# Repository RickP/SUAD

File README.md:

# Shut up and die!

A hardware version of a bomb defusing game.

Made with a custom board and a Raspberry Pi Pico.
The firmware supplies the manual over a USB mass storage medium.

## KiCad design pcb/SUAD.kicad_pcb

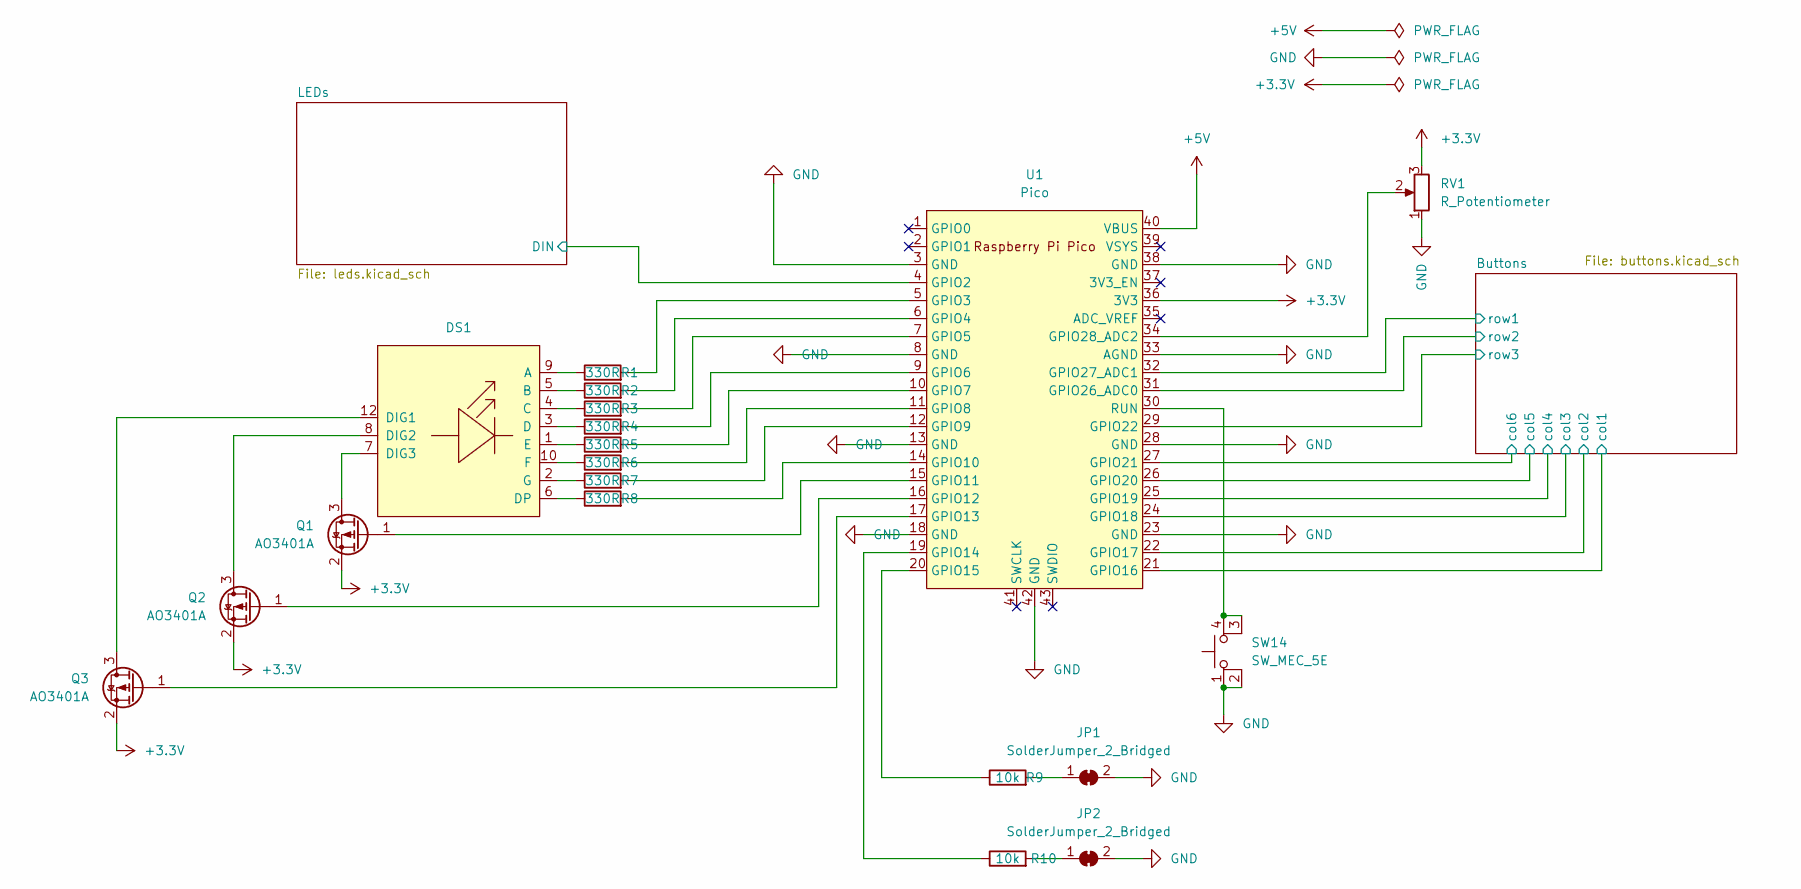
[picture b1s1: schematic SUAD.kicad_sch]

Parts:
DS1: SLS0563DRA1GD; LCSC C226010
JP1, JP2: SolderJumper_2_Bridged; SolderJumper-2_P1.3mm_Bridged_RoundedPad1.0x1.5mm
Q1, Q2, Q3: AO3401A; SOT-23; LCSC C15127
R1, R2, R3, R4, R5, R6, R7, R8: 330R; R_0603_1608Metric; LCSC C23138
R9, R10: 10k; R_0603_1608Metric; LCSC C25804
RV1: R_Potentiometer; RK10J11R001Y; LCSC C470765
SW14: SW_MEC_5E; TS-1187A-B-A-B; LCSC C318884
U1: Pico; RPi_Pico_SMD_TH

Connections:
+3V3: Q1.2 (S), Q2.2 (S), Q3.2 (S), RV1.3, U1.36 (3V3)
+5V: U1.40 (VBUS); also elsewhere on the board
/Buttons/col1: U1.21 (GPIO16); also elsewhere on the board
/Buttons/col2: U1.22 (GPIO17); also elsewhere on the board
/Buttons/col3: U1.24 (GPIO18); also elsewhere on the board
/Buttons/col4: U1.25 (GPIO19); also elsewhere on the board
/Buttons/col5: U1.26 (GPIO20); also elsewhere on the board
/Buttons/col6: U1.27 (GPIO21); also elsewhere on the board
/Buttons/row1: U1.32 (GPIO27_ADC1); also elsewhere on the board
/Buttons/row2: U1.31 (GPIO26_ADC0); also elsewhere on the board
/Buttons/row3: U1.29 (GPIO22); also elsewhere on the board
/LEDs/DIN: U1.4 (GPIO2); also elsewhere on the board
GND: JP1.2 (B), JP2.2 (B), RV1.1, SW14.1, SW14.2, U1.3 (GND), U1.8 (GND), U1.13 (GND), U1.18 (GND), U1.23 (GND), U1.28 (GND), U1.33 (AGND), U1.38 (GND), U1.42 (GND); also elsewhere on the board
unnamed: DS1.1 (E), R5.1
unnamed: DS1.2 (G), R7.1
unnamed: DS1.3 (D), R4.1
unnamed: DS1.4 (C), R3.1
unnamed: DS1.5 (B), R2.1
unnamed: DS1.6 (DP), R8.1
unnamed: DS1.7 (DIG3), Q1.3 (D)
unnamed: DS1.8 (DIG2), Q2.3 (D)
unnamed: DS1.9 (A), R1.1
unnamed: DS1.10 (F), R6.1
unnamed: DS1.12 (DIG1), Q3.3 (D)
unnamed: JP1.1 (A), R9.2
unnamed: JP2.1 (A), R10.2
unnamed: Q1.1 (G), U1.15 (GPIO11)
unnamed: Q2.1 (G), U1.16 (GPIO12)
unnamed: Q3.1 (G), U1.17 (GPIO13)
unnamed: R1.2, U1.5 (GPIO3)
unnamed: R2.2, U1.6 (GPIO4)
unnamed: R3.2, U1.7 (GPIO5)
unnamed: R4.2, U1.9 (GPIO6)
unnamed: R5.2, U1.10 (GPIO7)
unnamed: R6.2, U1.11 (GPIO8)
unnamed: R7.2, U1.12 (GPIO9)
unnamed: R8.2, U1.14 (GPIO10)
unnamed: R9.1, U1.20 (GPIO15)
unnamed: R10.1, U1.19 (GPIO14)
unnamed: RV1.2, U1.34 (GPIO28_ADC2)
unnamed: SW14.3 (K), SW14.4 (A), U1.30 (RUN)

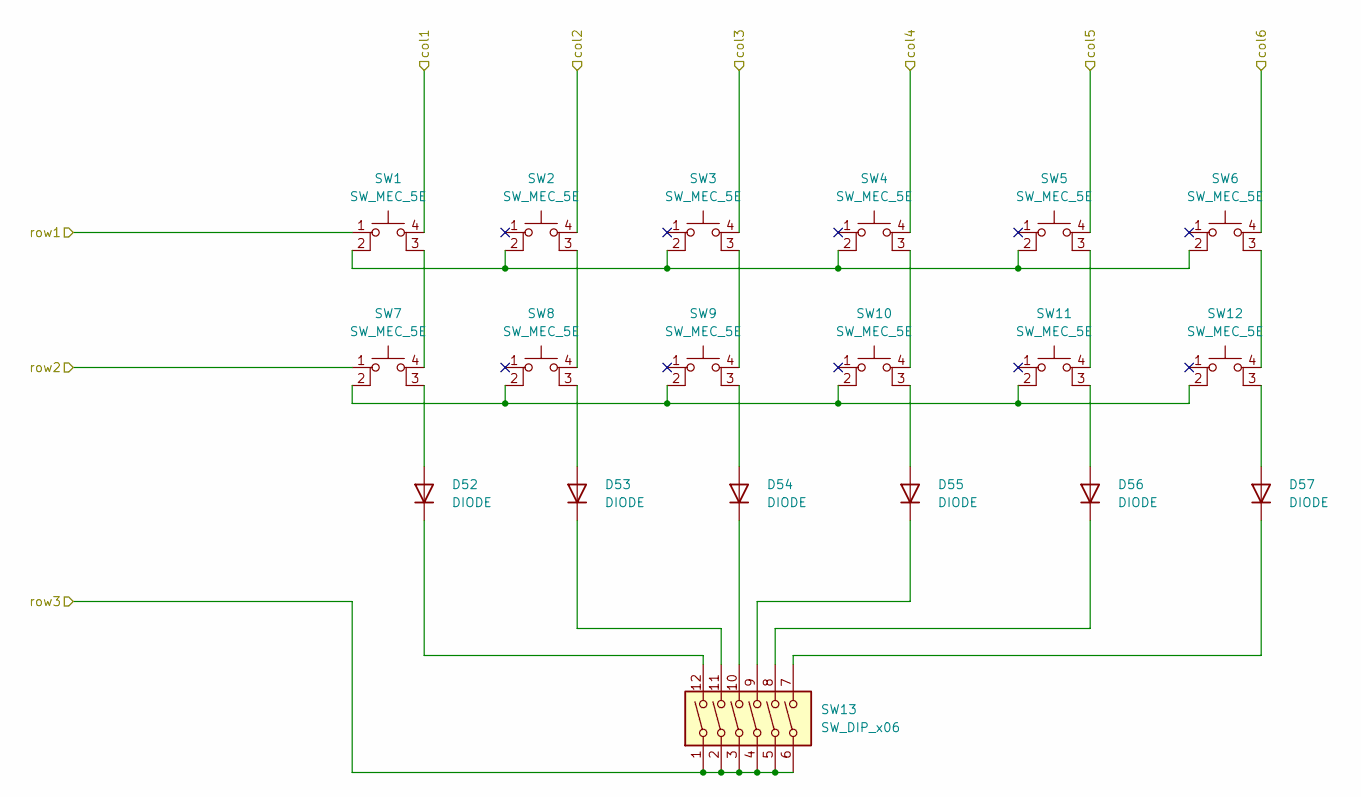
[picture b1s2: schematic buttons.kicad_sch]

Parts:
D52, D53, D54, D55, D56, D57: DIODE; D_SOD-123F; LCSC C64898
SW1, SW2, SW3, SW4, SW5, SW6, SW7, SW8, SW9, SW10, SW11, SW12: SW_MEC_5E; TS-1187A-B-A-B; LCSC C318884
SW13: SW_DIP_x06; SW_DIP_SPSTx06_Slide_6.7x16.8mm_W6.73mm_P2.54mm_LowProfile_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; LCSC C54952

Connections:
/Buttons/col1: SW1.4 (A); also elsewhere on the board
/Buttons/col2: SW2.4 (A); also elsewhere on the board
/Buttons/col3: SW3.4 (A); also elsewhere on the board
/Buttons/col4: SW4.4 (A); also elsewhere on the board
/Buttons/col5: SW5.4 (A); also elsewhere on the board
/Buttons/col6: SW6.4 (A); also elsewhere on the board
/Buttons/row1: SW1.1; also elsewhere on the board
/Buttons/row2: SW7.1; also elsewhere on the board
/Buttons/row3: SW13.1, SW13.2, SW13.3, SW13.4, SW13.5, SW13.6; also elsewhere on the board
unnamed: D52.1 (K), SW13.12
unnamed: D52.2 (A), SW7.3 (K)
unnamed: D53.1 (K), SW13.11
unnamed: D53.2 (A), SW8.3 (K)
unnamed: D54.1 (K), SW13.10
unnamed: D54.2 (A), SW9.3 (K)
unnamed: D55.1 (K), SW13.9
unnamed: D55.2 (A), SW10.3 (K)
unnamed: D56.1 (K), SW13.8
unnamed: D56.2 (A), SW11.3 (K)
unnamed: D57.1 (K), SW13.7
unnamed: D57.2 (A), SW12.3 (K)
unnamed: SW1.2, SW2.2, SW3.2, SW4.2, SW5.2, SW6.2
unnamed: SW1.3 (K), SW7.4 (A)
unnamed: SW2.3 (K), SW8.4 (A)
unnamed: SW3.3 (K), SW9.4 (A)
unnamed: SW7.2, SW8.2, SW9.2, SW10.2, SW11.2, SW12.2
unnamed: SW4.3 (K), SW10.4 (A)
unnamed: SW5.3 (K), SW11.4 (A)
unnamed: SW6.3 (K), SW12.4 (A)

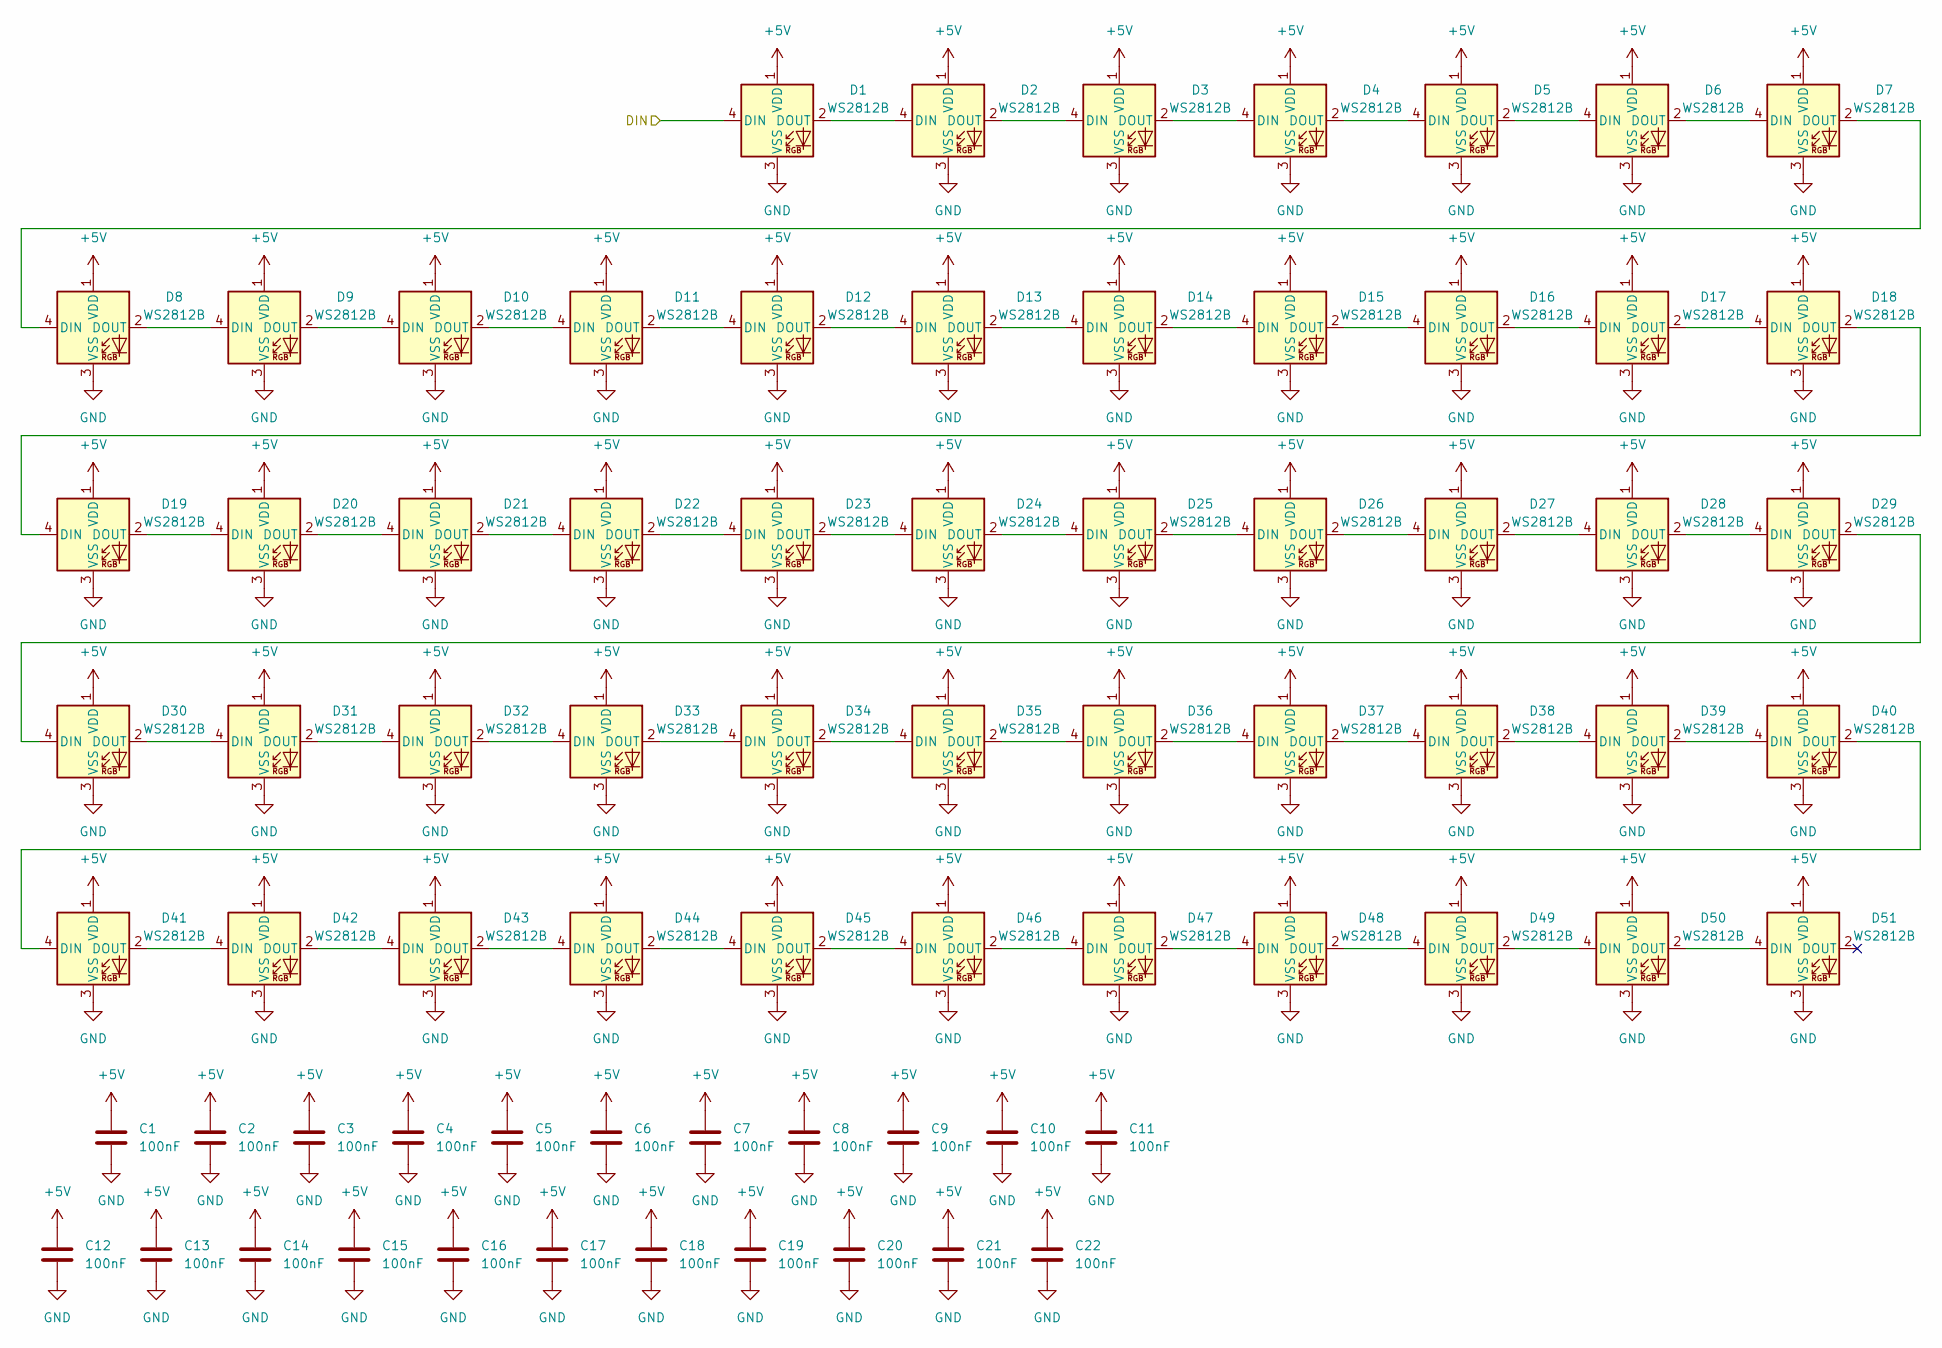
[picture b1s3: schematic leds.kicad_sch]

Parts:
C1, C2, C3, C4, C5, C6, C7, C8, C9, C10, C11, C12, C13, C14, C15, C16, C17, C18, C19, C20, C21, C22: 100nF; C_0603_1608Metric; LCSC C14663
D1, D2, D3, D4, D5, D6, D7, D8, D9, D10, D11, D12, D13, D14, D15, D16, D17, D18, D19, D20, D21, D22, D23, D24, D25, D26, D27, D28, D29, D30, D31, D32, D33, D34, D35, D36, D37, D38, D39, D40, D41, D42, D43, D44, D45, D46, D47, D48, D49, D50, D51: WS2812B; LED_WS2812B-Mini_3.5x3.5mm; LCSC C2890364

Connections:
+5V: C1.1, C2.1, C3.1, C4.1, C5.1, C6.1, C7.1, C8.1, C9.1, C10.1, C11.1, C12.1, C13.1, C14.1, C15.1, C16.1, C17.1, C18.1, C19.1, C20.1, C21.1, C22.1, D1.1 (VDD), D2.1 (VDD), D3.1 (VDD), D4.1 (VDD), D5.1 (VDD), D6.1 (VDD), D7.1 (VDD), D8.1 (VDD), D9.1 (VDD), D10.1 (VDD), D11.1 (VDD), D12.1 (VDD), D13.1 (VDD), D14.1 (VDD), D15.1 (VDD), D16.1 (VDD), D17.1 (VDD), D18.1 (VDD), D19.1 (VDD), D20.1 (VDD), D21.1 (VDD), D22.1 (VDD), D23.1 (VDD), D24.1 (VDD), D25.1 (VDD), D26.1 (VDD), D27.1 (VDD), D28.1 (VDD), D29.1 (VDD), D30.1 (VDD), D31.1 (VDD), D32.1 (VDD), D33.1 (VDD), D34.1 (VDD), D35.1 (VDD), D36.1 (VDD), D37.1 (VDD), D38.1 (VDD), D39.1 (VDD), D40.1 (VDD), D41.1 (VDD), D42.1 (VDD), D43.1 (VDD), D44.1 (VDD), D45.1 (VDD), D46.1 (VDD), D47.1 (VDD), D48.1 (VDD), D49.1 (VDD), D50.1 (VDD), D51.1 (VDD); also elsewhere on the board
/LEDs/DIN: D1.4 (DIN); also elsewhere on the board
GND: C1.2, C2.2, C3.2, C4.2, C5.2, C6.2, C7.2, C8.2, C9.2, C10.2, C11.2, C12.2, C13.2, C14.2, C15.2, C16.2, C17.2, C18.2, C19.2, C20.2, C21.2, C22.2, D1.3 (VSS), D2.3 (VSS), D3.3 (VSS), D4.3 (VSS), D5.3 (VSS), D6.3 (VSS), D7.3 (VSS), D8.3 (VSS), D9.3 (VSS), D10.3 (VSS), D11.3 (VSS), D12.3 (VSS), D13.3 (VSS), D14.3 (VSS), D15.3 (VSS), D16.3 (VSS), D17.3 (VSS), D18.3 (VSS), D19.3 (VSS), D20.3 (VSS), D21.3 (VSS), D22.3 (VSS), D23.3 (VSS), D24.3 (VSS), D25.3 (VSS), D26.3 (VSS), D27.3 (VSS), D28.3 (VSS), D29.3 (VSS), D30.3 (VSS), D31.3 (VSS), D32.3 (VSS), D33.3 (VSS), D34.3 (VSS), D35.3 (VSS), D36.3 (VSS), D37.3 (VSS), D38.3 (VSS), D39.3 (VSS), D40.3 (VSS), D41.3 (VSS), D42.3 (VSS), D43.3 (VSS), D44.3 (VSS), D45.3 (VSS), D46.3 (VSS), D47.3 (VSS), D48.3 (VSS), D49.3 (VSS), D50.3 (VSS), D51.3 (VSS); also elsewhere on the board
unnamed: D1.2 (DOUT), D2.4 (DIN)
unnamed: D2.2 (DOUT), D3.4 (DIN)
unnamed: D3.2 (DOUT), D4.4 (DIN)
unnamed: D4.2 (DOUT), D5.4 (DIN)
unnamed: D5.2 (DOUT), D6.4 (DIN)
unnamed: D6.2 (DOUT), D7.4 (DIN)
unnamed: D7.2 (DOUT), D8.4 (DIN)
unnamed: D8.2 (DOUT), D9.4 (DIN)
unnamed: D10.2 (DOUT), D11.4 (DIN)
unnamed: D9.2 (DOUT), D10.4 (DIN)
unnamed: D11.2 (DOUT), D12.4 (DIN)
unnamed: D12.2 (DOUT), D13.4 (DIN)
unnamed: D13.2 (DOUT), D14.4 (DIN)
unnamed: D14.2 (DOUT), D15.4 (DIN)
unnamed: D15.2 (DOUT), D16.4 (DIN)
unnamed: D16.2 (DOUT), D17.4 (DIN)
unnamed: D17.2 (DOUT), D18.4 (DIN)
unnamed: D18.2 (DOUT), D19.4 (DIN)
unnamed: D19.2 (DOUT), D20.4 (DIN)
unnamed: D20.2 (DOUT), D21.4 (DIN)
unnamed: D21.2 (DOUT), D22.4 (DIN)
unnamed: D22.2 (DOUT), D23.4 (DIN)
unnamed: D23.2 (DOUT), D24.4 (DIN)
unnamed: D24.2 (DOUT), D25.4 (DIN)
unnamed: D25.2 (DOUT), D26.4 (DIN)
unnamed: D26.2 (DOUT), D27.4 (DIN)
unnamed: D27.2 (DOUT), D28.4 (DIN)
unnamed: D28.2 (DOUT), D29.4 (DIN)
unnamed: D29.2 (DOUT), D30.4 (DIN)
unnamed: D30.2 (DOUT), D31.4 (DIN)
unnamed: D31.2 (DOUT), D32.4 (DIN)
unnamed: D32.2 (DOUT), D33.4 (DIN)
unnamed: D33.2 (DOUT), D34.4 (DIN)
unnamed: D34.2 (DOUT), D35.4 (DIN)
unnamed: D35.2 (DOUT), D36.4 (DIN)
unnamed: D36.2 (DOUT), D37.4 (DIN)
unnamed: D37.2 (DOUT), D38.4 (DIN)
unnamed: D38.2 (DOUT), D39.4 (DIN)
unnamed: D39.2 (DOUT), D40.4 (DIN)
unnamed: D40.2 (DOUT), D41.4 (DIN)
unnamed: D41.2 (DOUT), D42.4 (DIN)
unnamed: D42.2 (DOUT), D43.4 (DIN)
unnamed: D43.2 (DOUT), D44.4 (DIN)
unnamed: D44.2 (DOUT), D45.4 (DIN)
unnamed: D45.2 (DOUT), D46.4 (DIN)
unnamed: D46.2 (DOUT), D47.4 (DIN)
unnamed: D47.2 (DOUT), D48.4 (DIN)
unnamed: D48.2 (DOUT), D49.4 (DIN)
unnamed: D49.2 (DOUT), D50.4 (DIN)
unnamed: D50.2 (DOUT), D51.4 (DIN)

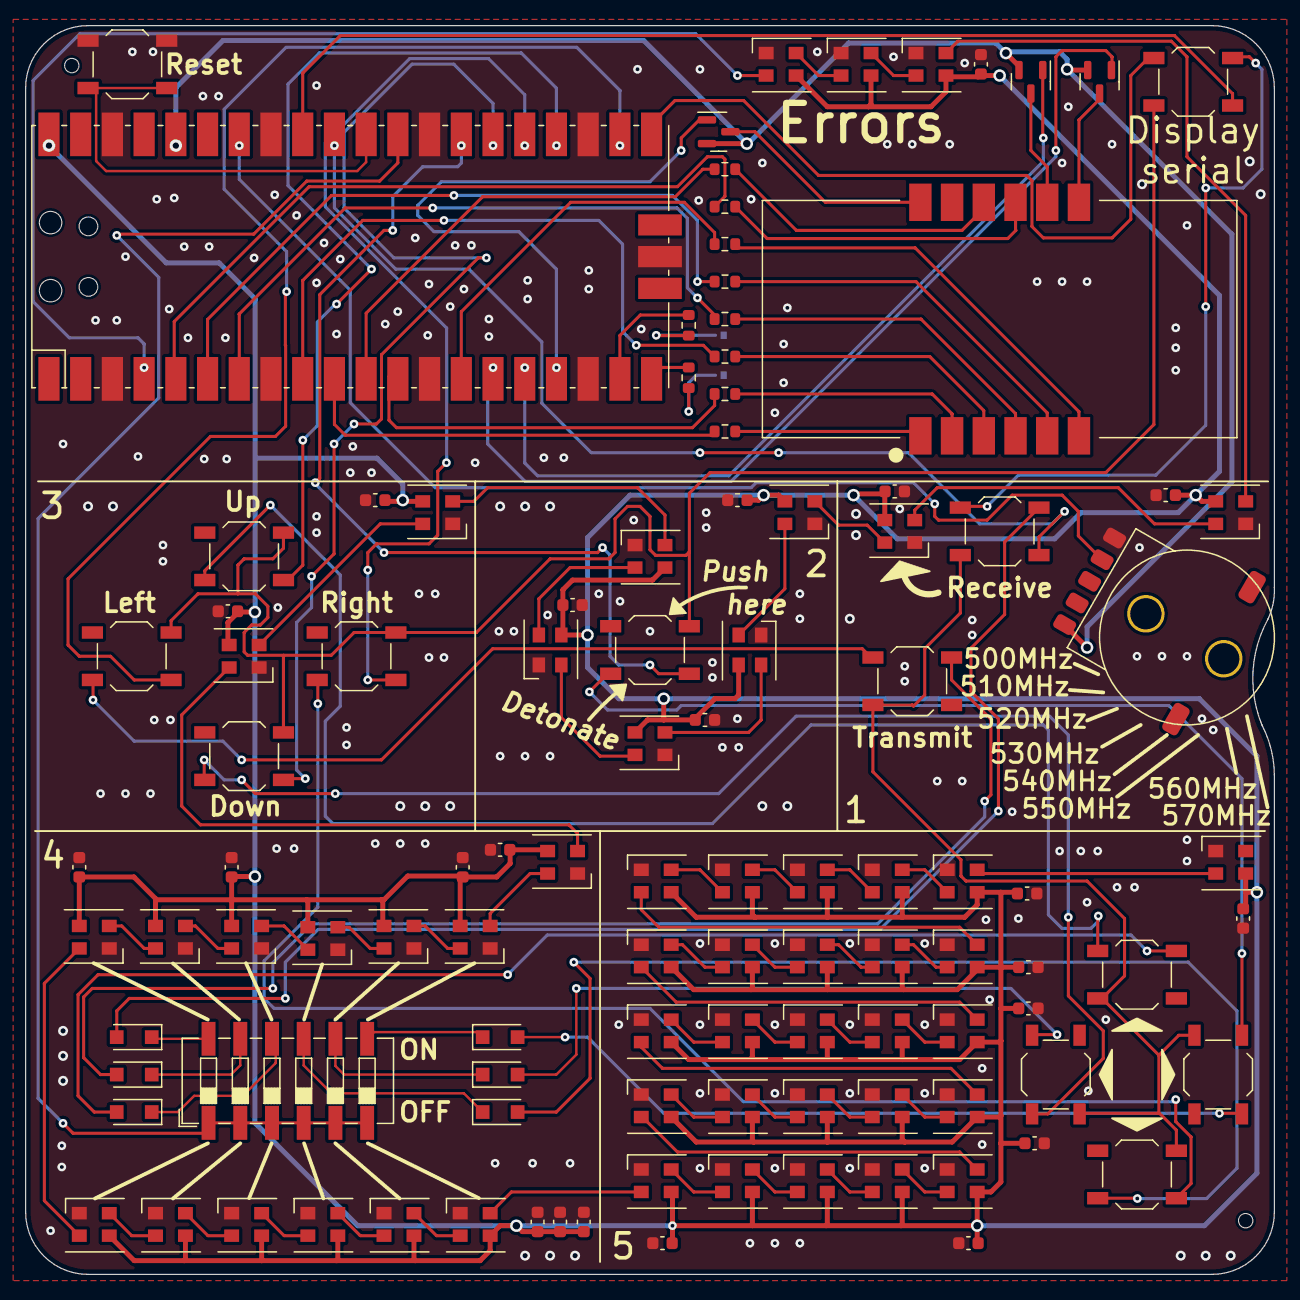
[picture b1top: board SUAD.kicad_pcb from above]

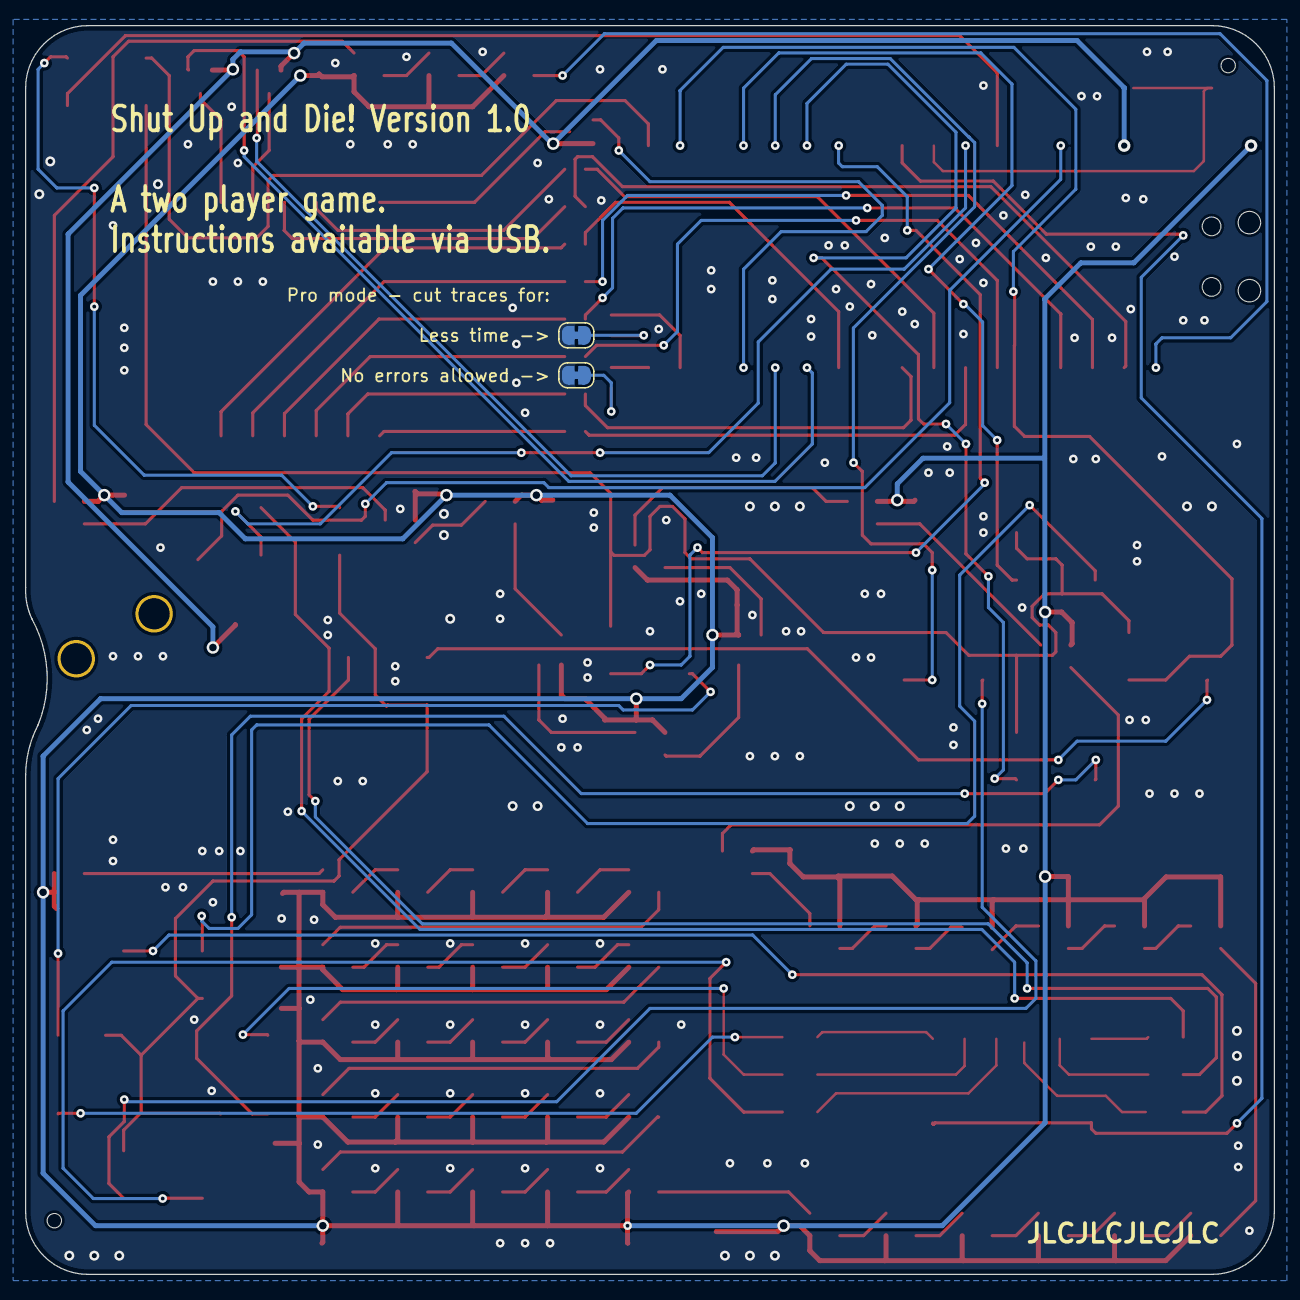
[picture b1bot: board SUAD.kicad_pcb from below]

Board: 2 copper layers, 100.0 x 100.0 mm, 111 parts (2 on the bottom side), 111 nets.

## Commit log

2022-02-07 Added pcb
2022-02-07 added workflow
2022-02-07 workflow trigger
2022-02-08 Routed
2022-02-08 Fixed ERC and DRC
2022-02-08 use older kibot image
2022-02-09 Changed kibot config
2022-02-15 Added firmware
2022-02-22 Implemented segment display and keyscan
2022-02-23 Added thread safety
2022-02-23 Got rid of fifo; Optimized WS2812 driver
2022-02-23 Use mask functions in display driver
2022-02-24 Added module handling, jumpers and fail/success"
2022-02-24 Added USB MSC stuff; Generate random serial
2022-02-25 USB stuff
2022-02-25 did stuff
2022-02-27 fat16
2022-02-27 Various fixes; better fat16 stuff
2022-02-28 Work on fat16 stuff
2022-02-28 Cleanups
2022-03-03 Added diodes to key matrix
2022-03-03 Finished module 1
2022-03-04 cleanup
2022-03-06 Implemented module 5
2022-03-06 Documentation
2022-03-06 Finished instructions
2022-03-06 Added manual PDF
2022-03-07 Improved RNG; Added module 2 code
2022-03-14 maintainance
2022-03-22 Small fixed for new board
2022-03-22 Feature completeness
2022-03-22 Small fixes
2022-03-22 Silkscreen and footprint improvements
2022-04-04 Fixes
2022-04-07 Fixed animations
2022-04-09 PCB changes
2022-10-20 Added vscode debug files
2022-12-27 Added serial output
2024-11-04 Updated SDK
2024-11-08 firmware fixes
2024-11-08 Moved usb task to core0
2024-11-09 Removed USB CDC
